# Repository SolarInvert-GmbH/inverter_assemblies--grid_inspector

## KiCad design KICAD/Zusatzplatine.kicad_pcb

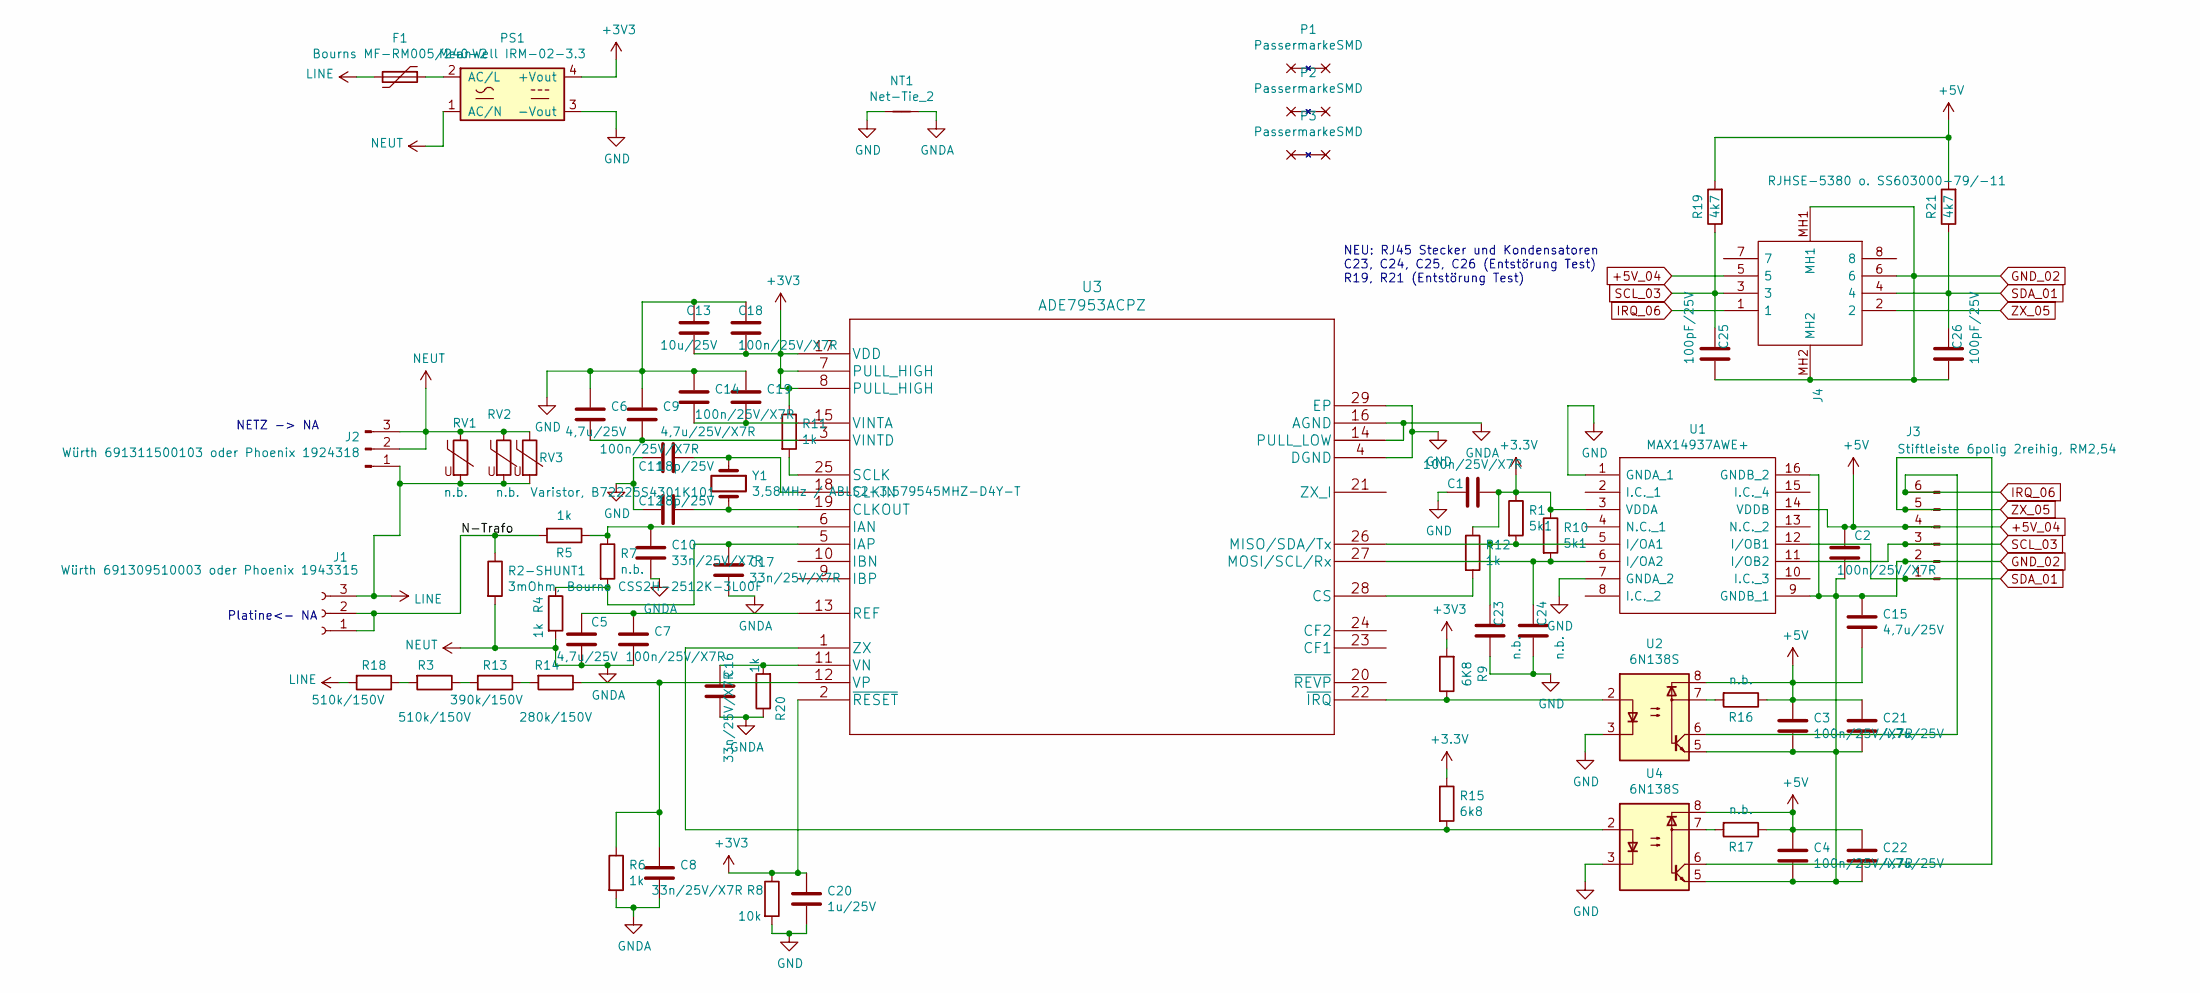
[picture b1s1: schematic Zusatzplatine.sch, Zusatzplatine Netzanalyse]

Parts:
C1, C2, C3, C4, C7, C9, C18, C19: 100n/25V/X7R; C_0805
C5, C6, C15, C21, C22: 4,7u/25V; C_0805
C8, C10, C16, C17: 33n/25V/X7R; C_0805
C11, C12: 18p/25V; C_0805
C13: 10u/25V; C_1206
C14: 4,7u/25V/X7R; C_0805
C20: 1u/25V; C_0805
C23, C24: n.b.; C_0805_2012Metric
C25, C26: 100pF/25V; C_0805_2012Metric
F1: Bourns MF-RM005/240-2; RV_Disc_D9_W4.1_P5
J1: Würth 691309510003 oder Phoenix 1943315; Sauro_CGF039M5_03x5.08mm_Angled
J2: Würth 691311500103 oder Phoenix 1924318; PhoenixContact_MSTBVA-G_03x5.08mm_Vertical
J3: Stiftleiste 6polig 2reihig, RM2,54; Pin_Header_Straight_2x03_Pitch2.54mm
J4: RJHSE-5380 o. SS603000-79/-11; RJHSE5380-SS603000-11o79merge; Mouser Part Number 523-RJHSE-5380
NT1: Net-Tie_2; NetTie-I_Connected_SMD
P1, P2, P3: PassermarkeSMD; Passermarke_d1d3
PS1: MeanWell IRM-02-3.3; ACDC-Conv_THTMeanWell-IRM-02-XX
R1, R10: 5k1; R_0805_2012Metric
R2-SHUNT1: 3mOhm, Bourns CSS2H-2512K-3L00F; R_2512_6332_Metric_Shunt
R3, R18: 510k/150V; R_0805_2012Metric
R4, R5, R6, R11, R12, R20: 1k; R_0805_2012Metric
R7, R16, R17: n.b.; R_0805_2012Metric
R8: 10k; R_0805_2012Metric
R9: 6K8; R_0805_2012Metric
R13: 390k/150V; R_0805_2012Metric
R14: 280k/150V; R_0805_2012Metric
R15: 6k8; R_0805_2012Metric
R19, R21: 4k7; R_0805_2012Metric
RV1: n.b.; RV_Disc_D21.5_W4.9_P10
RV2: n.b.; RV_Disc_D12_W4.8_P7.5
RV3: Varistor, B72225S4301K101; RV_Disc_D27.5_W6.3_P12.7
U1: MAX14937AWE+; SOIC-16W_7.5x10.3mm_Pitch1.27mm; Manufacturer_Part_Number MAX14937AWE+
U2, U4: 6N138S; SMDIP-8_W9.53mm_Clearance8mm
U3: ADE7953ACPZ
Y1: 3,58MHz / ABLS2-3.579545MHZ-D4Y-T; Crystal_SMD_SeikoEpson_MC405-2pin_9.6x4.1mm_HandSoldering

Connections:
+5V_04: C2.1, C3.1, C4.1, C15.2, C21.1, C22.1, J3.4, J4.5, R16.1, R17.1, R19.2, R21.2, U1.14 (VDDB), U2.8, U4.8
/N-Trafo: J1.1, J1.2, R2-SHUNT1.1, R5.2
GND: C1.2, C6.2, C9.2, C11.2, C12.2, C13.2, C14.2, C18.1, C19.2, C20.2, C23.1, C24.1, NT1.1, PS1.3 (-Vout), R8.2, U1.1 (GNDA_1), U1.7 (GNDA_2), U2.3, U3.4 (DGND), U3.29 (EP), U4.3
GNDA: C5.2, C7.2, C8.2, C10.2, C16.1, C17.2, J2.2, J2.3, NT1.2, PS1.1 (AC/N), R2-SHUNT1.2, R4.2, R6.2, R20.1, RV1.1, RV2.1, RV3.1, U3.14 (PULL_LOW), U3.16 (AGND)
GND_02: C2.2, C3.2, C4.2, C15.1, C21.2, C22.2, C25.1, C26.1, J3.2, J4.6, J4.MH1, J4.MH2, U1.9 (GNDB_1), U1.16 (GNDB_2), U2.5, U4.5
IRQ_06: J3.6, J4.1, U2.6
LINE: F1.2, J1.3, J2.1, R18.2, RV1.2, RV2.2, RV3.2
unnamed: C5.1, C7.1, U3.13 (REF)
unnamed: C6.1, C9.1, U3.3 (VINTD)
unnamed: C8.1, R6.1, R14.1, U3.12 (VP)
unnamed: C10.1, R5.1, R7.1, U3.6 (IAN)
unnamed: C11.1, U3.18 (CLKIN), Y1.1
unnamed: C12.1, U3.19 (CLKOUT), Y1.2
unnamed: C14.1, C19.1, U3.15 (VINTA)
unnamed: C16.2, R20.2, U3.11 (VN)
unnamed: C17.1, R4.1, R7.2, U3.5 (IAP)
unnamed: C23.2, R1.2, U1.5 (I/OA1), U3.26 (MISO/SDA/Tx)
unnamed: C24.2, R10.2, U1.6 (I/OA2), U3.27 (MOSI/SCL/Rx)
unnamed: F1.1, PS1.2 (AC/L)
unnamed: R9.1, U2.2, U3.22 (~IRQ)
unnamed: R11.2, U3.25 (SCLK)
unnamed: R12.2, U3.28 (CS)
unnamed: R13.1, R14.2
unnamed: R3.1, R13.2
unnamed: R15.2, U3.1 (ZX), U4.2
unnamed: R16.2, U2.7
unnamed: R17.2, U4.7
unnamed: R3.2, R18.1
SCL_03: C25.2, J3.3, J4.3, R19.1, U1.11 (I/OB2)
SDA_01: C26.2, J3.1, J4.4, R21.1, U1.12 (I/OB1)
ZX_05: J3.5, J4.2, U4.6

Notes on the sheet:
NEU: RJ45 Stecker und Kondensatoren C23, C24, C25, C26 (Entstörung Test) R19, R21 (Entstörung Test)
NETZ -> NA
Platine<- NA

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
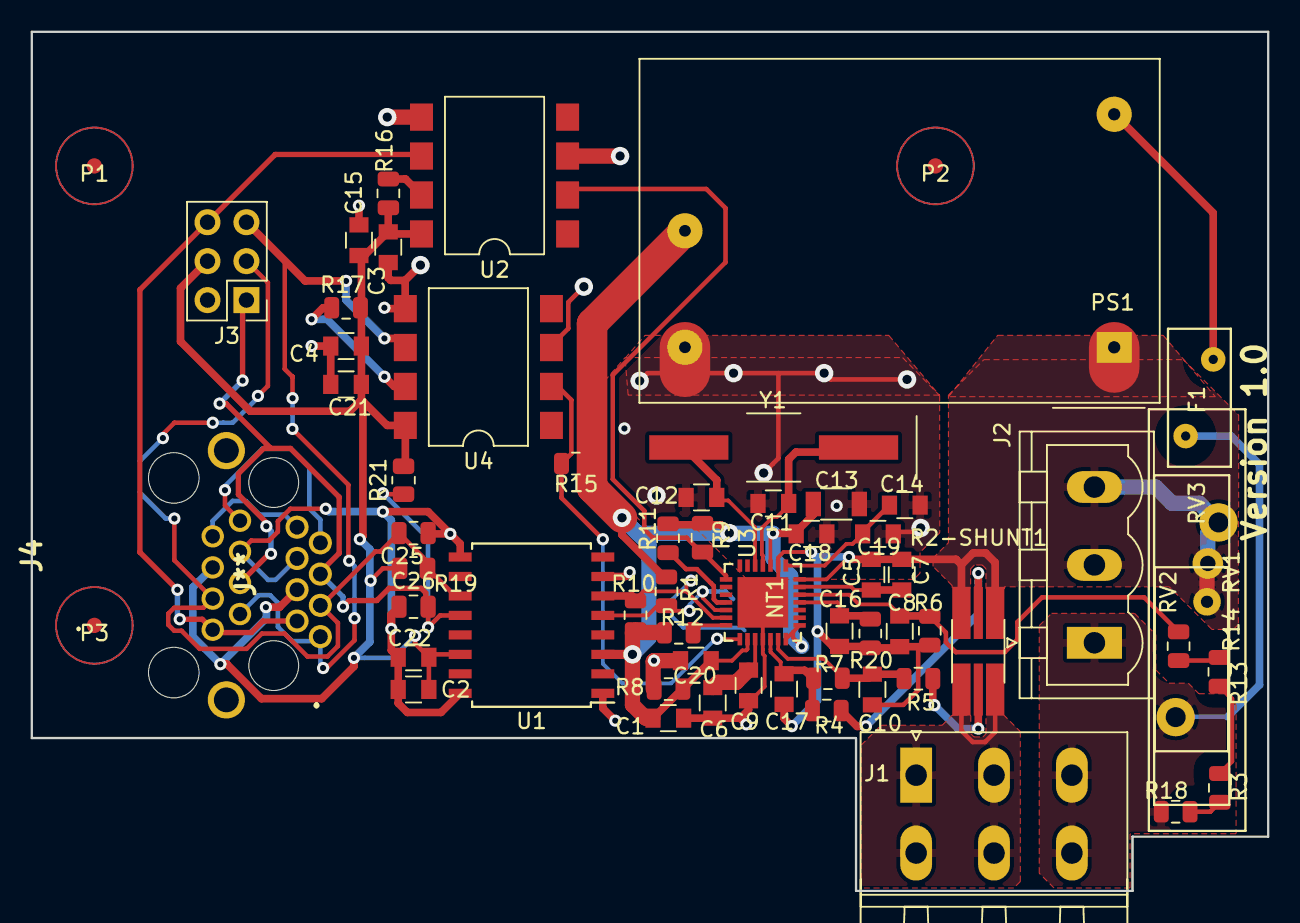
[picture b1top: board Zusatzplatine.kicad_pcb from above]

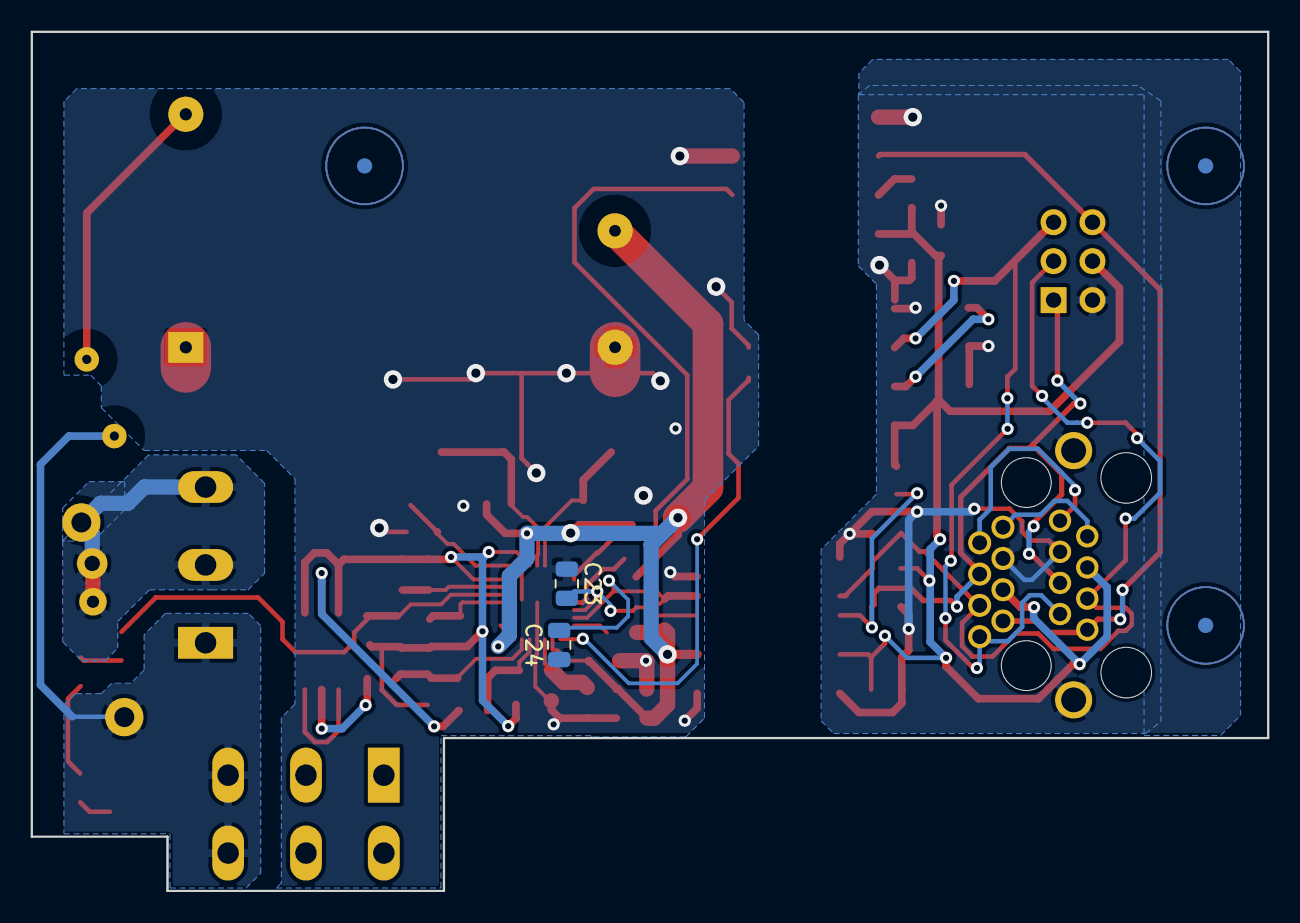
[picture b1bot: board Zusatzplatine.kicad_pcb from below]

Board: 2 copper layers, 80.7 x 56.0 mm, 65 parts (2 on the bottom side), 32 nets.

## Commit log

2023-05-11 First Upload

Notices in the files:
parts and their libraries:
Copyright 2016 Accelerated Designs. All rights reserved.
